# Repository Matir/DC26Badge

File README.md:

# Attacker Community DEF CON 26 Badge #

This is an unofficial #badgelife DEF CON 26 badge for the Attacker Community.

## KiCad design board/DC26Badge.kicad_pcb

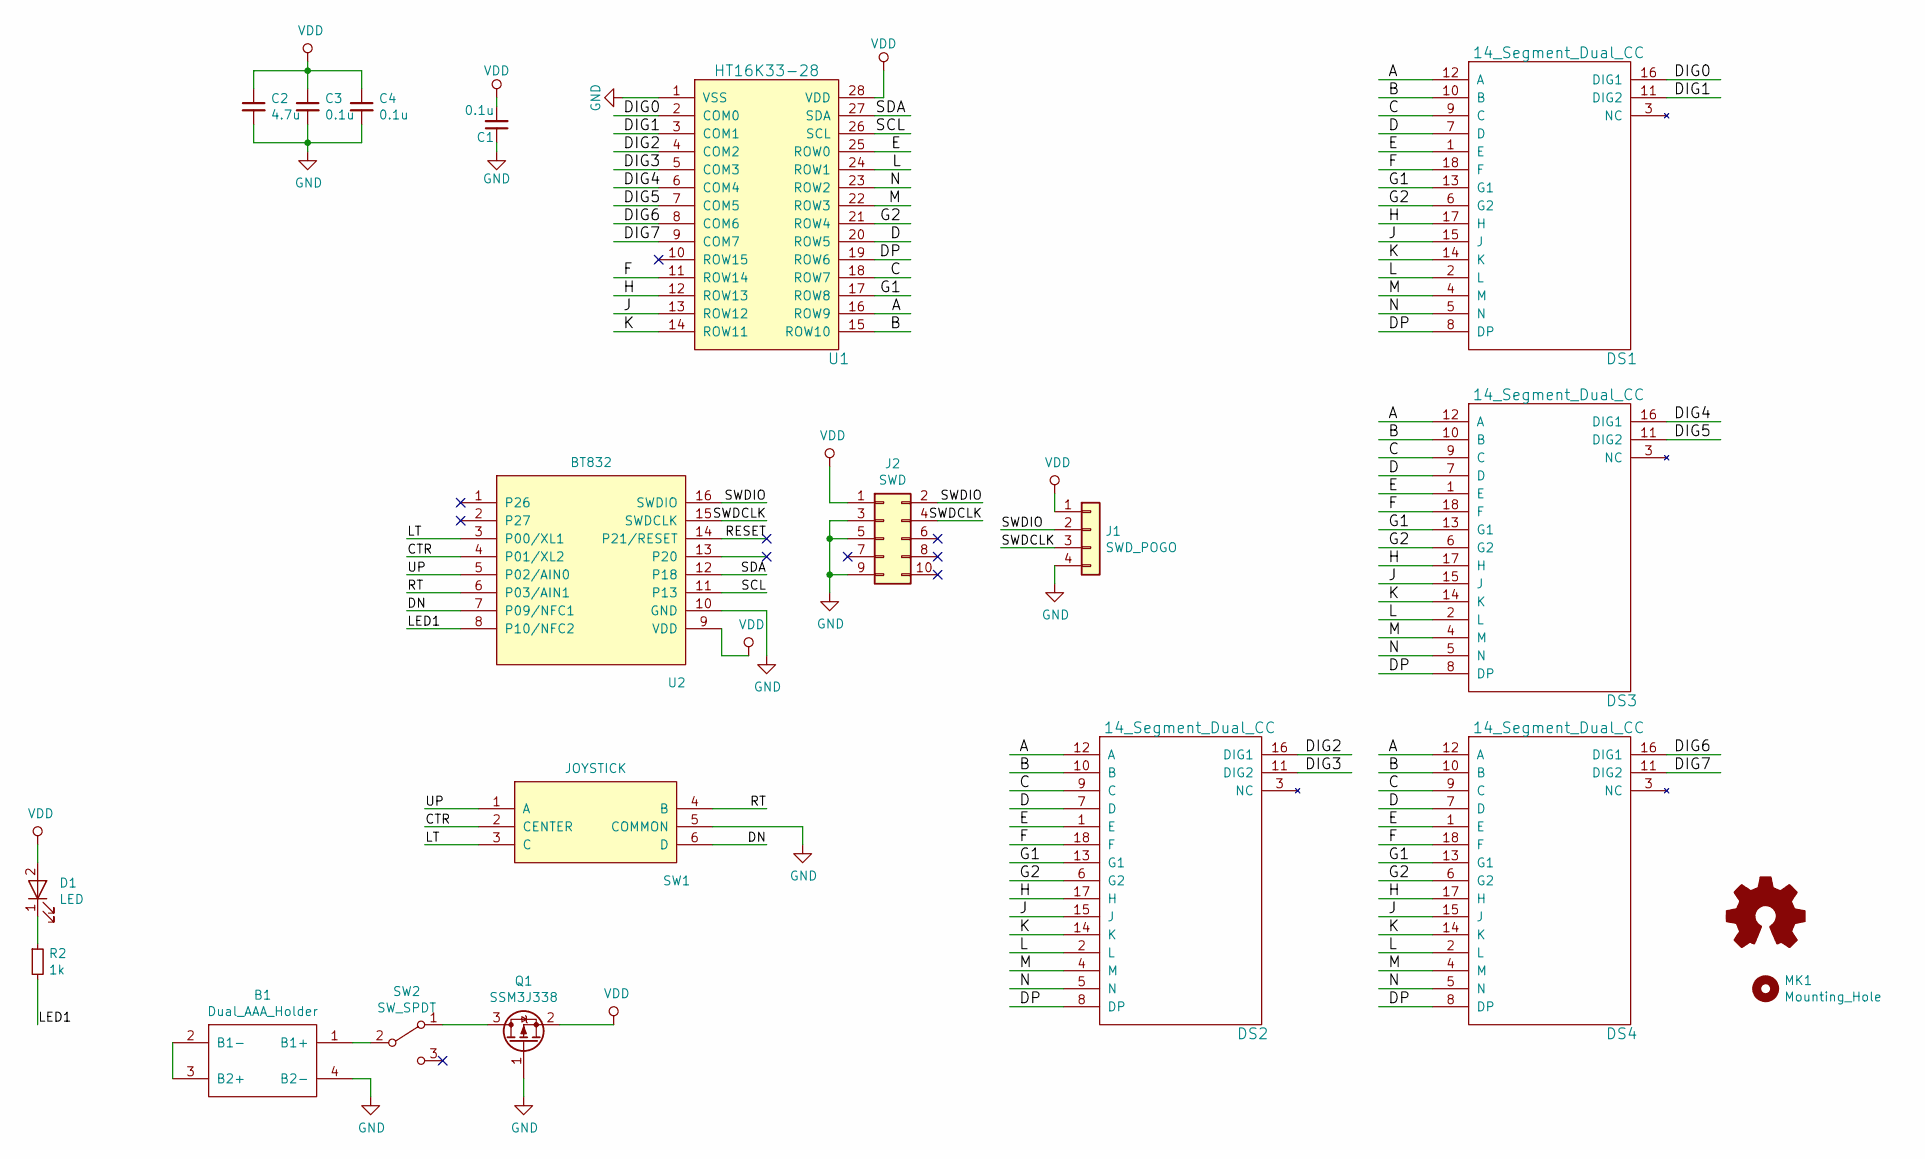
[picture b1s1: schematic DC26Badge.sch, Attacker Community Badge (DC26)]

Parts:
B1: Dual_AAA_Holder; Keystone_1022
C1, C3, C4: 0.1u; C_0603_1608Metric
C2: 4.7u; C_0603_1608Metric
D1: LED; LED_0603_1608Metric
DS1, DS2, DS3, DS4: 14_Segment_Dual_CC; DUAL_14SEG
J1: SWD_POGO
J2: SWD; PinHeader_2x05_P1.27mm_Vertical_SMD
MK1: Mounting_Hole; MountingHole_3.2mm_M3
Q1: SSM3J338; SOT-23_Handsoldering
R2: 1k; R_0603_1608Metric
SW1: JOYSTICK
SW2: SW_SPDT; JS102011SAQN
U1: HT16K33-28; HT16K133
U2: BT832

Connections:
/A: DS1.12 (A), DS2.12 (A), DS3.12 (A), DS4.12 (A), U1.16 (ROW9)
/B: DS1.10 (B), DS2.10 (B), DS3.10 (B), DS4.10 (B), U1.15 (ROW10)
/C: DS1.9 (C), DS2.9 (C), DS3.9 (C), DS4.9 (C), U1.18 (ROW7)
/CTR: SW1.2 (CENTER), U2.4 (P01/XL2)
/D: DS1.7 (D), DS2.7 (D), DS3.7 (D), DS4.7 (D), U1.20 (ROW5)
/DIG0: DS1.16 (DIG1), U1.2 (COM0)
/DIG1: DS1.11 (DIG2), U1.3 (COM1)
/DIG2: DS2.16 (DIG1), U1.4 (COM2)
/DIG3: DS2.11 (DIG2), U1.5 (COM3)
/DIG4: DS3.16 (DIG1), U1.6 (COM4)
/DIG5: DS3.11 (DIG2), U1.7 (COM5)
/DIG6: DS4.16 (DIG1), U1.8 (COM6)
/DIG7: DS4.11 (DIG2), U1.9 (COM7)
/DN: SW1.6 (D), U2.7 (P09/NFC1)
/DP: DS1.8 (DP), DS2.8 (DP), DS3.8 (DP), DS4.8 (DP), U1.19 (ROW6)
/E: DS1.1 (E), DS2.1 (E), DS3.1 (E), DS4.1 (E), U1.25 (ROW0)
/F: DS1.18 (F), DS2.18 (F), DS3.18 (F), DS4.18 (F), U1.11 (ROW14)
/G1: DS1.13 (G1), DS2.13 (G1), DS3.13 (G1), DS4.13 (G1), U1.17 (ROW8)
/G2: DS1.6 (G2), DS2.6 (G2), DS3.6 (G2), DS4.6 (G2), U1.21 (ROW4)
/H: DS1.17 (H), DS2.17 (H), DS3.17 (H), DS4.17 (H), U1.12 (ROW13)
/J: DS1.15 (J), DS2.15 (J), DS3.15 (J), DS4.15 (J), U1.13 (ROW12)
/K: DS1.14 (K), DS2.14 (K), DS3.14 (K), DS4.14 (K), U1.14 (ROW11)
/L: DS1.2 (L), DS2.2 (L), DS3.2 (L), DS4.2 (L), U1.24 (ROW1)
/LED1: R2.2, U2.8 (P10/NFC2)
/LT: SW1.3 (C), U2.3 (P00/XL1)
/M: DS1.4 (M), DS2.4 (M), DS3.4 (M), DS4.4 (M), U1.22 (ROW3)
/N: DS1.5 (N), DS2.5 (N), DS3.5 (N), DS4.5 (N), U1.23 (ROW2)
/RESET: U2.14 (P21/RESET)
/RT: SW1.4 (B), U2.6 (P03/AIN1)
/SCL: U1.26 (SCL), U2.11 (P13)
/SDA: U1.27 (SDA), U2.12 (P18)
/SWDCLK: J1.3, J2.4, U2.15 (SWDCLK)
/SWDIO: J1.2, J2.2, U2.16 (SWDIO)
/UP: SW1.1 (A), U2.5 (P02/AIN0)
GND: B1.4 (B2-), C1.1, C2.2, C3.2, C4.2, J1.4, J2.3, J2.5, J2.9, Q1.1 (G), SW1.5 (COMMON), U1.1 (VSS), U2.10 (GND)
unnamed: B1.1 (B1+), SW2.2 (B)
unnamed: B1.2 (B1-), B1.3 (B2+)
unnamed: D1.1 (K), R2.1
unnamed: Q1.3 (D), SW2.1 (A)
VDD: C1.2, C2.1, C3.1, C4.1, D1.2 (A), J1.1, J2.1, Q1.2 (S), U1.28 (VDD), U2.9 (VDD)

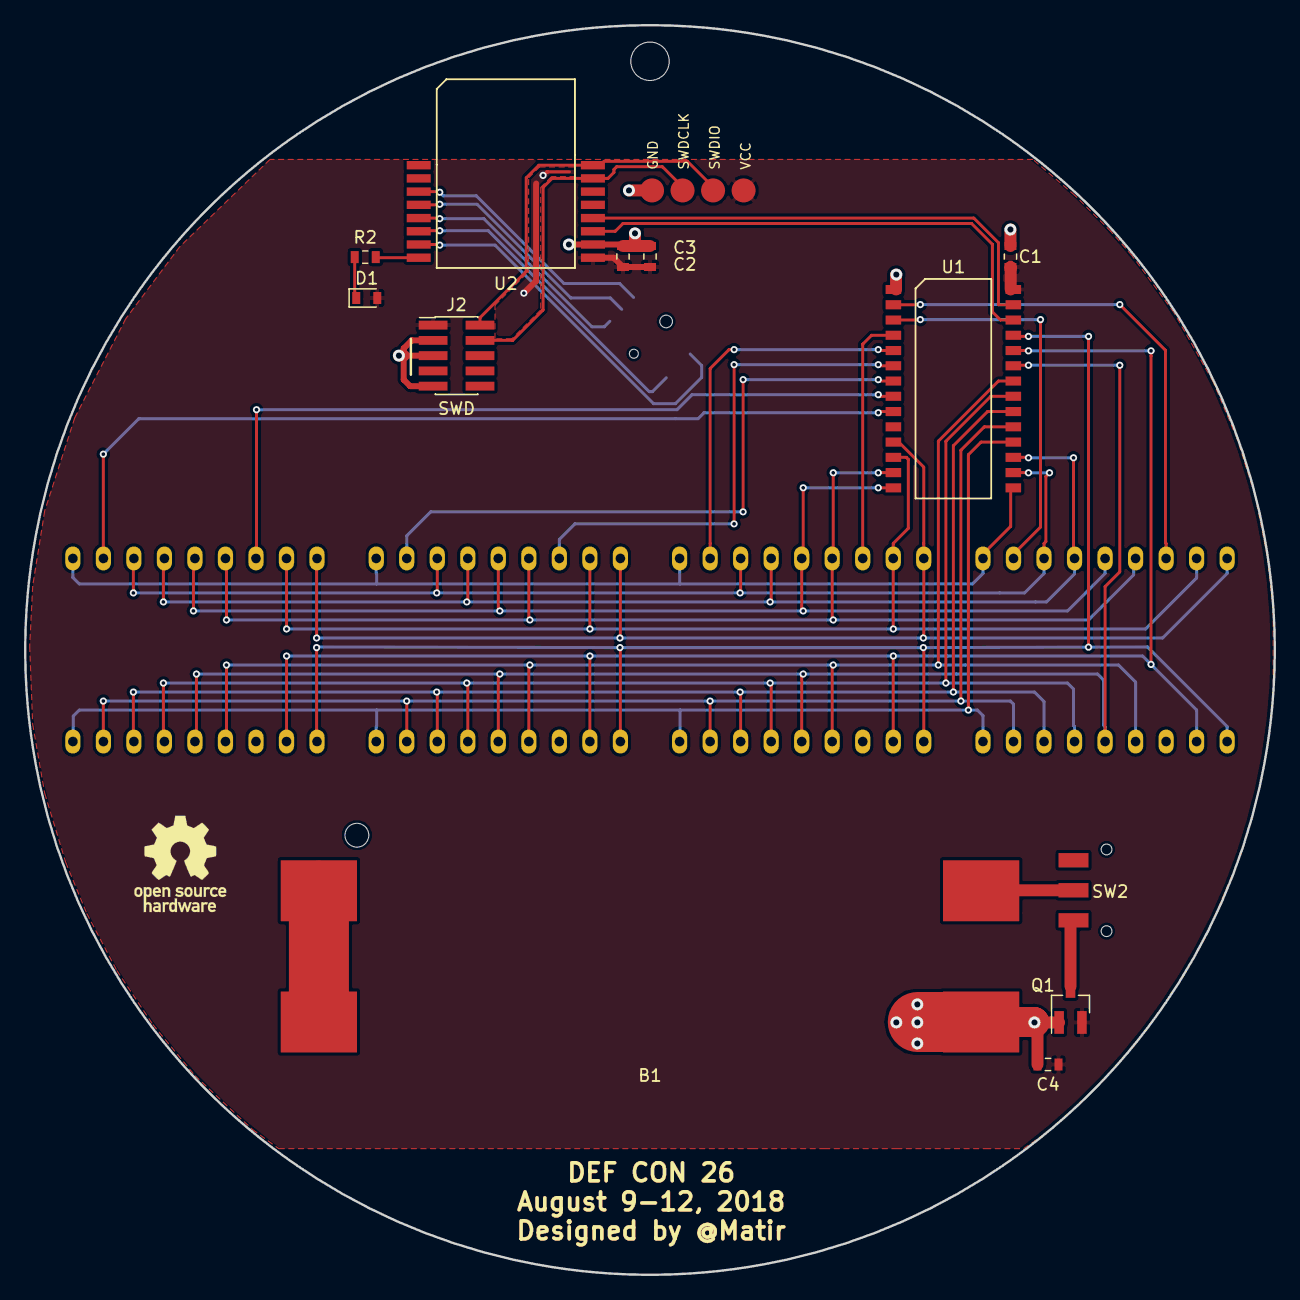
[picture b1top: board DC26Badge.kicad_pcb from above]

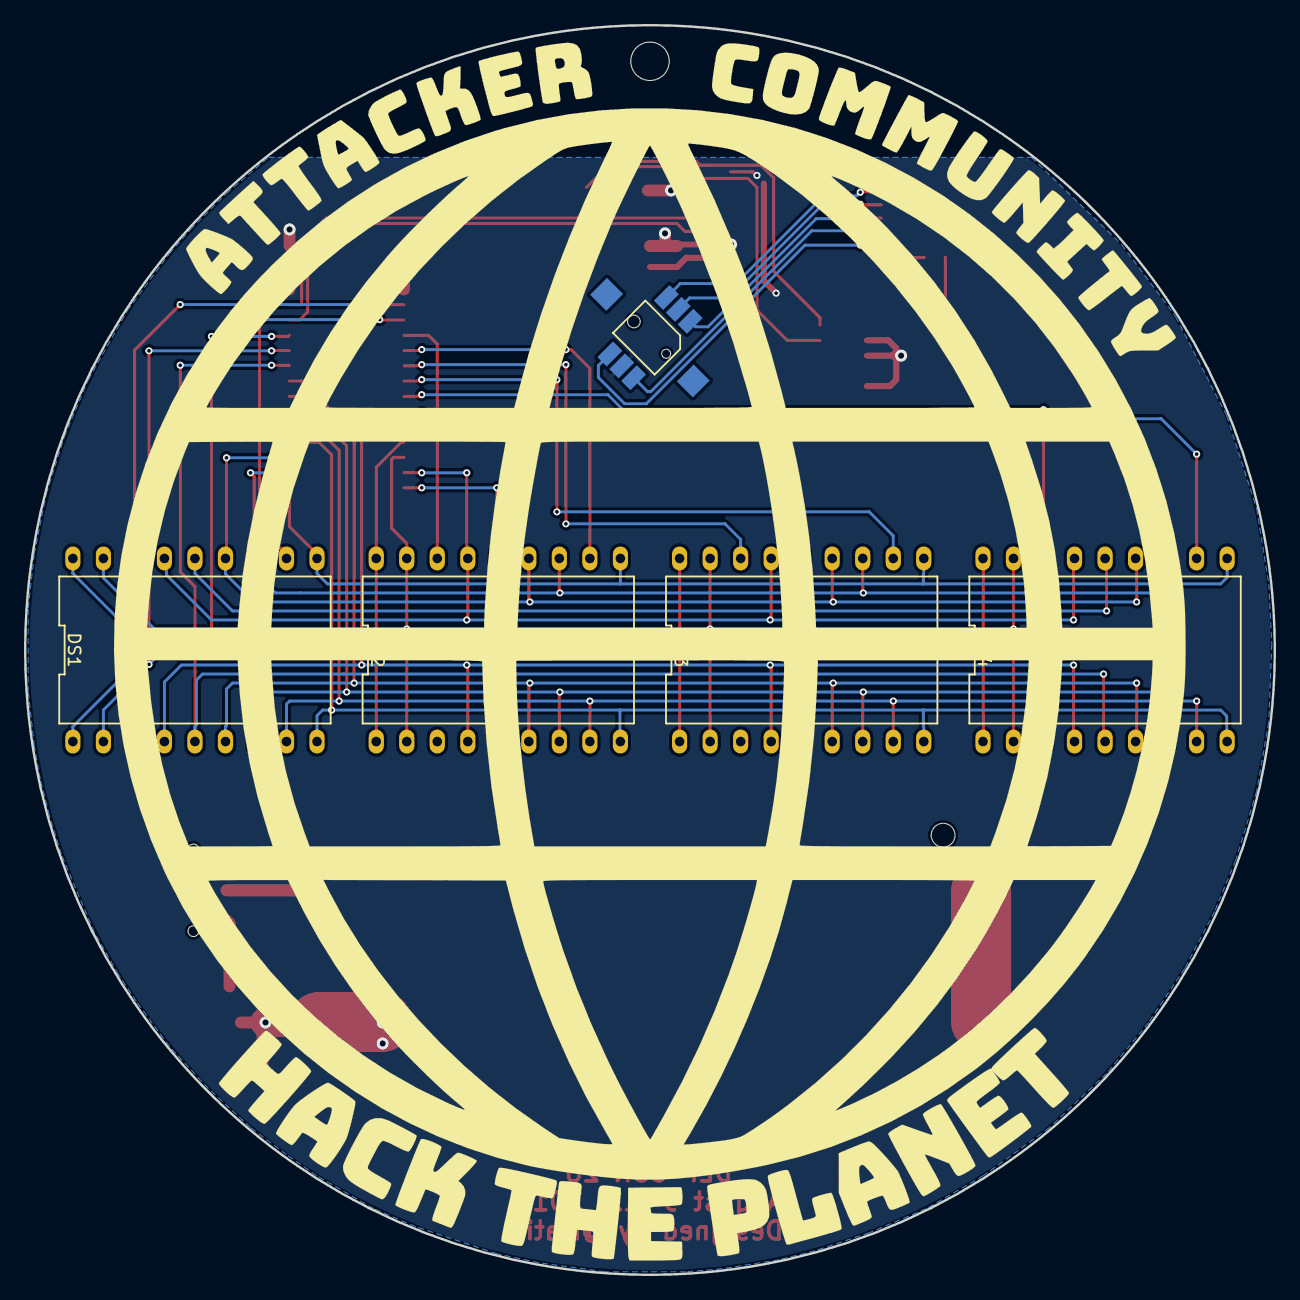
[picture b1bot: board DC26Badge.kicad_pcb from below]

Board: 2 copper layers, 104.0 x 104.0 mm, 19 parts (5 on the bottom side), 39 nets.

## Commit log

2018-05-02 Start initial work on new badge.
2018-05-05 Rearrange, create skeleton firmware.
2018-05-06 Script to build font.
2018-05-06 Minimal working display of "HACK"
2018-05-07 It scrolls!
2018-05-07 Progress?
2018-05-08 Can turn badge on/off via BLE.
2018-05-10 Prototype schematic finished.
2018-05-10 Work on parts.
2018-05-10 BT832 component.
2018-05-11 First pass of prototype PCB layout.
2018-05-12 Prototype R1.
2018-05-13 BLE stays connected.
2018-05-13 Allow changing of messages over BLE.
2018-05-13 Fix size of displays.
2018-05-13 Prepare for security.
2018-05-13 Minimal button support.
2018-05-13 Remove accidental log.
2018-05-13 Commit sdk_config.
2018-05-14 Start work on LESC support.
2018-05-14 Compiles and runs.
2018-05-14 Add pairing with display.
2018-05-17 Working LESC support!
2018-05-17 Add QWR support.
2018-05-20 Fix order of operations for BLE, run without 32k XTAL.
2018-05-20 Create segment map for badge.
2018-05-20 Footprint fixes.
2018-05-21 Do first circular board.
2018-05-21 Background.
2018-05-21 Add TODO
2018-05-23 Add copyright.
2018-05-23 Fix silkscreen.
2018-05-25 Fix up board.
2018-05-26 Add programmer adapter board.
2018-05-27 Add schematic from prototype r1.
2018-05-27 Fix BLE in firmware.
2018-05-27 Add initial android app.
2018-05-28 Can scan for devices.
2018-05-28 Forward progress on app.
2018-05-29 Progress, but need to serialize GATT Operations... fml.
2018-05-29 More progress, but still a long way to go.
2018-05-29 Add TODO.
2018-05-30 Add support for brightness to BLE.
2018-05-30 API for using flash.
2018-06-01 Add final schematic.
2018-06-01 Bump .pro file.
2018-06-01 Add MSG_WARGAMES constant.
2018-06-01 Update TODO.
2018-06-01 Add defs for production board.
2018-06-01 Wire up the buttons.
2018-06-01 Load messages on startup.
2018-06-01 Save message on change.
2018-06-01 Device name save/restore.
2018-06-02 Update TODO from Android
2018-06-02 Improve firmware debugging.
2018-06-02 Better handle updates, though I'm not sure why.
2018-06-02 Add work on message list.
2018-06-02 Progress
2018-06-02 Support updates of messages.
2018-06-03 Support for changing currently active message.
2018-06-03 Fix some aspects of saving to flash.
2018-06-03 Track dirty state of messages with crc-32.
2018-06-03 Fix saving.
2018-06-03 Progress.
2018-06-03 Looks like name can be changed.
2018-06-03 Fixy.
2018-06-03 Add wargames mode. I think.
2018-06-03 Fix wargames mode.
2018-06-03 Add factory reset.
2018-06-04 Test my PRNG... good enough.
2018-06-05 Add circular scrolling.
2018-06-16 Build in a selftest on first boot/reset.
2018-07-08 Reset joystick after selftest.
2018-07-09 Show message when no badges found.
2018-07-09 Use better scrolling by default.
2018-07-09 Add an icon on previously used devices.
2018-07-09 Fix line between items in list.
2018-07-09 Remove unused menu.
2018-07-13 Ensure all records in a file are deleted.
2018-07-16 Update messages.
2018-07-16 Update android.
2018-07-21 Change scanning latency.
2018-07-21 Fix proto buttons.
2018-07-28 Fixes.
2018-07-30 Android 1.1 release.
2018-08-02 Add LICENSE, README.
